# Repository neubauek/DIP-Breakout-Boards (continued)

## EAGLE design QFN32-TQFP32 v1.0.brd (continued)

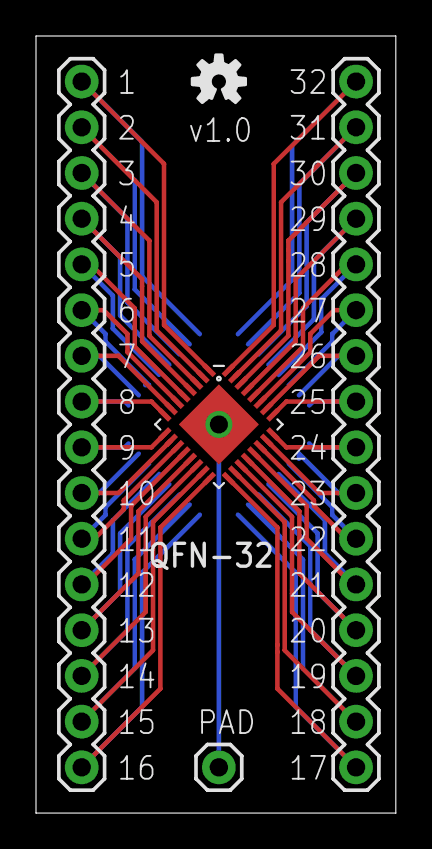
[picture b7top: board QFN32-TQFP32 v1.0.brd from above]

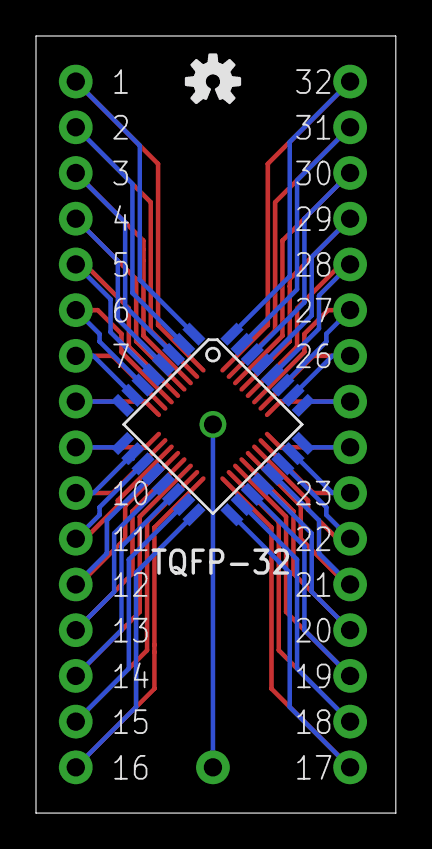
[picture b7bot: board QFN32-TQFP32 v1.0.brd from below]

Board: 2 copper layers, 20.0 x 43.2 mm, 8 parts (2 on the bottom side), 33 nets.

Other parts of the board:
U$1, U$2: OSHW-LOGO-S

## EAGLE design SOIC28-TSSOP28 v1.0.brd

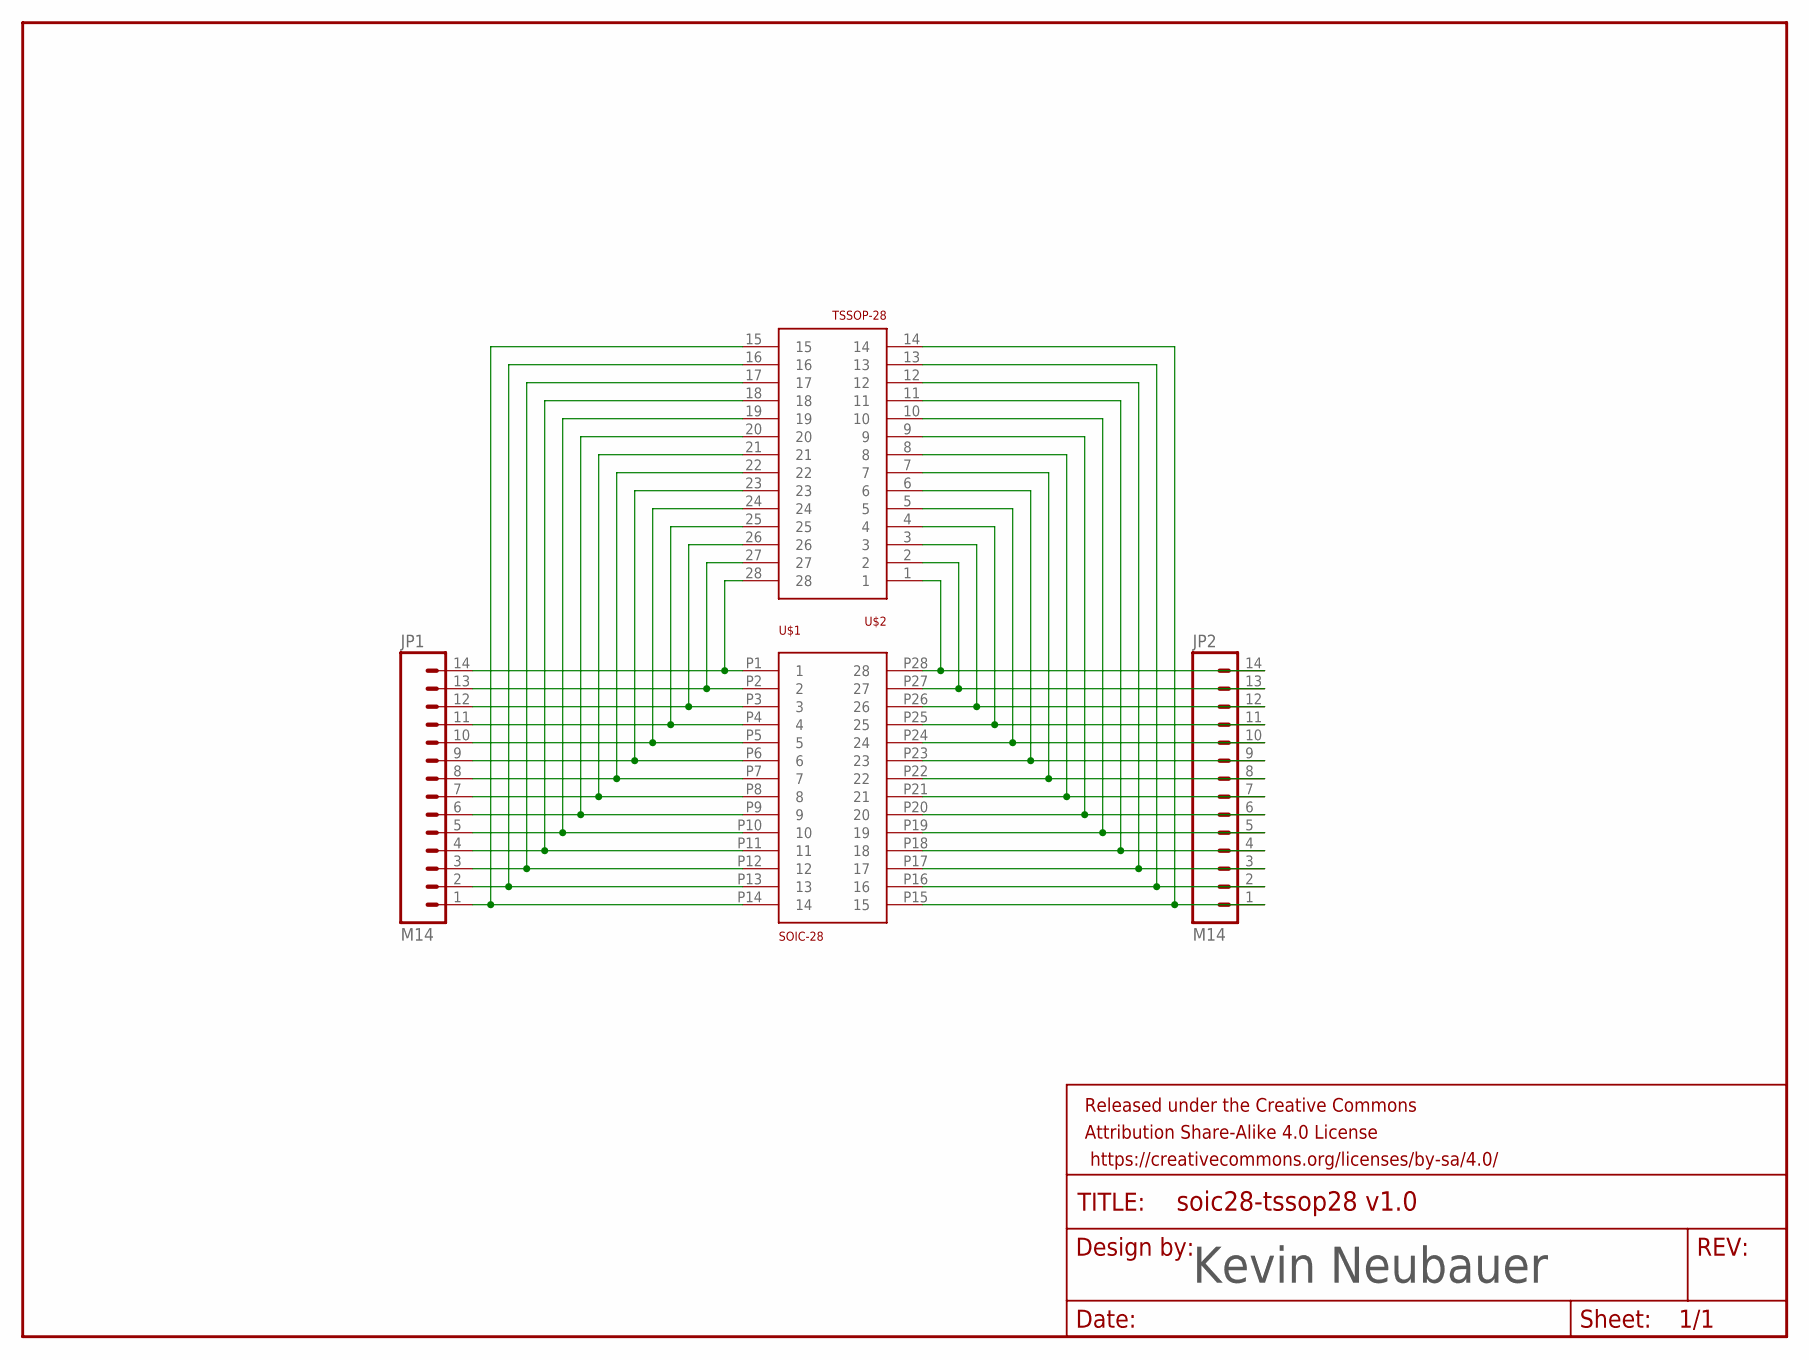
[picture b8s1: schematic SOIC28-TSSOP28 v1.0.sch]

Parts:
FRAME1: FRAME-LETTER; CREATIVE_COMMONS
JP1, JP2: M14; 1X14
U$1: SOIC-28
U$2: TSSOP-28; TSSOP28

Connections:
unnamed: JP1.14, U$1.P1 (1), U$2.28
unnamed: JP1.13, U$1.P2 (2), U$2.27
unnamed: JP2.14, U$1.P28 (28), U$2.1
unnamed: JP2.13, U$1.P27 (27), U$2.2
unnamed: JP2.12, U$1.P26 (26), U$2.3
unnamed: JP2.11, U$1.P25 (25), U$2.4
unnamed: JP2.10, U$1.P24 (24), U$2.5
unnamed: JP2.9, U$1.P23 (23), U$2.6
unnamed: JP2.8, U$1.P22 (22), U$2.7
unnamed: JP2.7, U$1.P21 (21), U$2.8
unnamed: JP2.6, U$1.P20 (20), U$2.9
unnamed: JP2.5, U$1.P19 (19), U$2.10
unnamed: JP1.2, U$1.P13 (13), U$2.16
unnamed: JP1.1, U$1.P14 (14), U$2.15
unnamed: JP2.4, U$1.P18 (18), U$2.11
unnamed: JP2.3, U$1.P17 (17), U$2.12
unnamed: JP2.2, U$1.P16 (16), U$2.13
unnamed: JP2.1, U$1.P15 (15), U$2.14
unnamed: JP1.3, U$1.P12 (12), U$2.17
unnamed: JP1.4, U$1.P11 (11), U$2.18
unnamed: JP1.5, U$1.P10 (10), U$2.19
unnamed: JP1.6, U$1.P9 (9), U$2.20
unnamed: JP1.8, U$1.P7 (7), U$2.22
unnamed: JP1.7, U$1.P8 (8), U$2.21
unnamed: JP1.10, U$1.P5 (5), U$2.24
unnamed: JP1.9, U$1.P6 (6), U$2.23
unnamed: JP1.12, U$1.P3 (3), U$2.26
unnamed: JP1.11, U$1.P4 (4), U$2.25

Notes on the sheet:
Kevin Neubauer

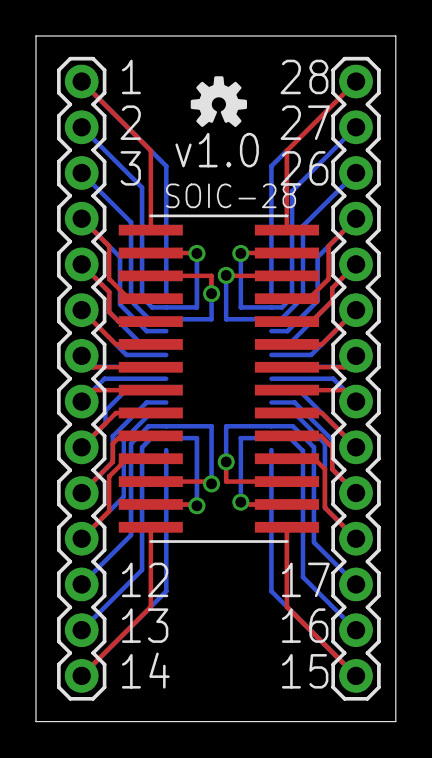
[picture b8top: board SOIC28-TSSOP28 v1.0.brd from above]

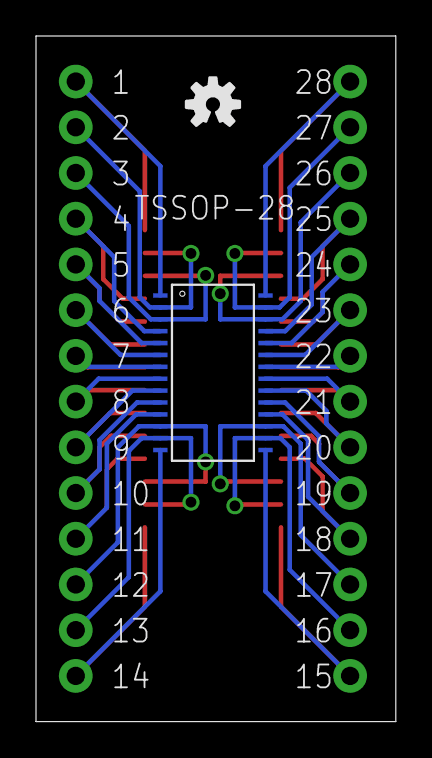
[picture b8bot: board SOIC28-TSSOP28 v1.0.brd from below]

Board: 2 copper layers, 20.0 x 38.1 mm, 7 parts (2 on the bottom side), 28 nets.

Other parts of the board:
U$3, U$4: OSHW-LOGO-S

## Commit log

2015-05-20 SMT to DIP Breakout Boards
    Breakout boards to convert SMT chips to DIP format for use in
    breadboard prototyping.
    These designs have all been validated against DirtyPCB and OSHPark
    design rules, but most have not been sent off to be fabricated.
    Be mindful of pitch size when using QFN components. I noticed when
    developing my QFN-28 board that not all QFN-28 chips are created with
2015-05-20 Added read and QFN28 panel board file
2015-05-28 Renamed QFN-28 boards to include 3mm chip size
2015-06-09 Fixed Silk on QFN32 and added SOT23
    Fixed silkscreen issue with QFN32-TQFP32
    Added SOT23-3 - SOT23-6 board.
2015-07-07 Silk and board revision
    Worked several silk screen issues and narrowed some boards.
2015-09-26 Added SOT223, SOT89, 1206, TO252
